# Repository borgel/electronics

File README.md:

Ultimate Hacking Keyboard electronics
=====================================

Contained are the schematics and board layout KiCad files for the [Ultimate Hacking Keyboard](https://ultimatehackingkeyboard.com/).

Please make sure to clone this repo with:

`git clone --recursive git@github.com:borgel/electronics.git`

Now, you should be able to open any of the 4 [KiCad](http://kicad-pcb.org/) projects of the repo:

* [left-main](left-main) contains main PCB of left keyboard half.
* [right-main](right-main) contains the main PCB of the right keyboard half.
* [display](display) contains the PCB that interfaces our custom manufactured LED segment display with the left main PCB.
* [connectors](connectors) are very small PCBs that are soldered vertically to the left and right main circuit boards to interconnect the keyboard halves without needing a bridge cable.

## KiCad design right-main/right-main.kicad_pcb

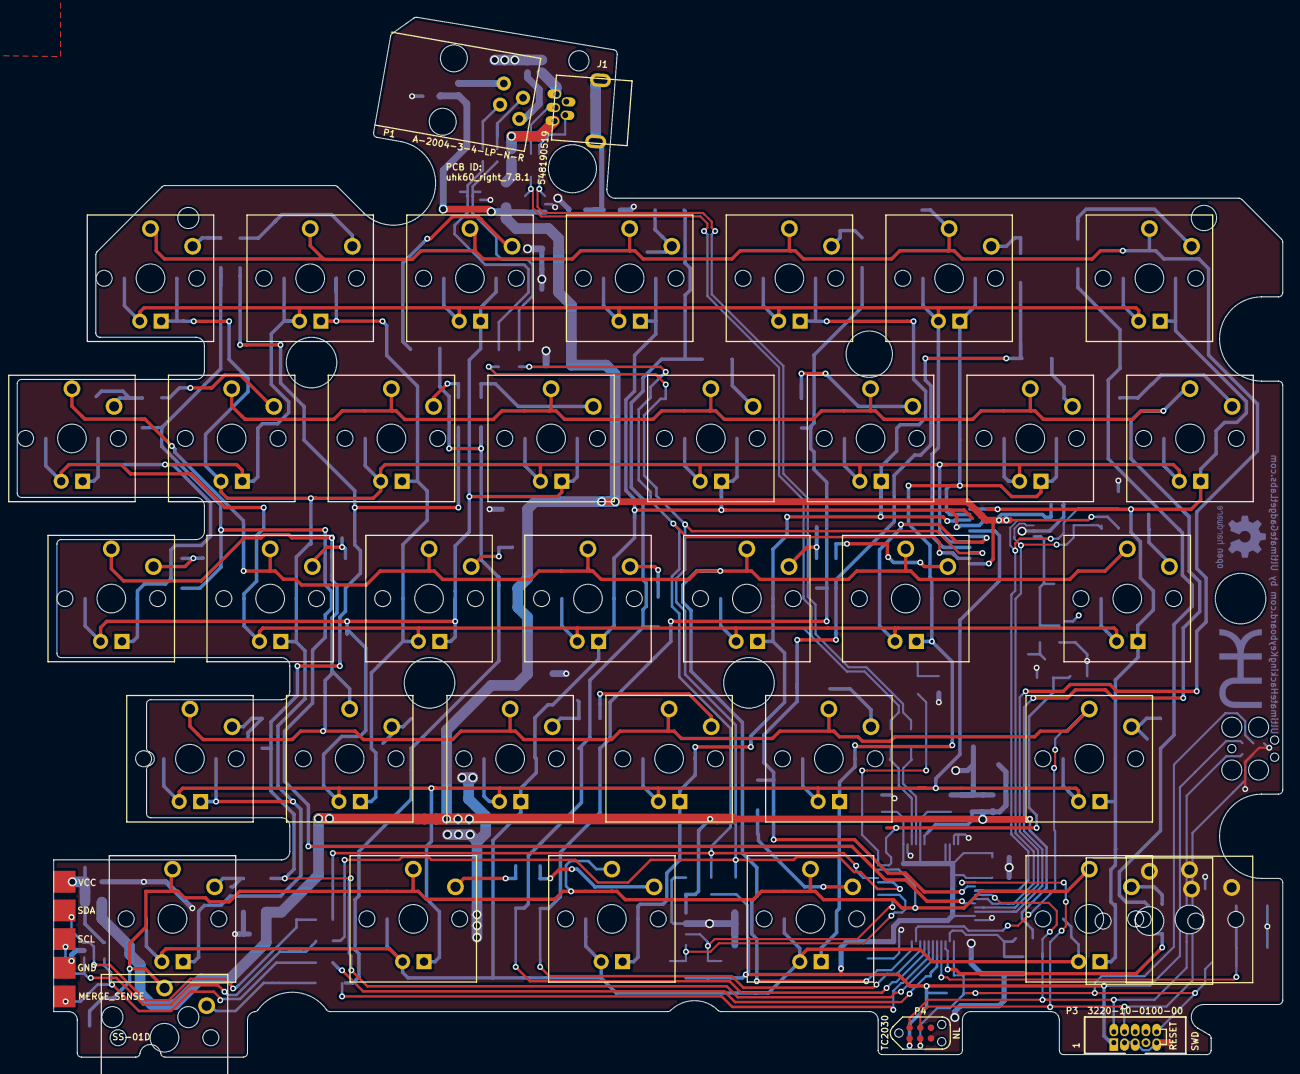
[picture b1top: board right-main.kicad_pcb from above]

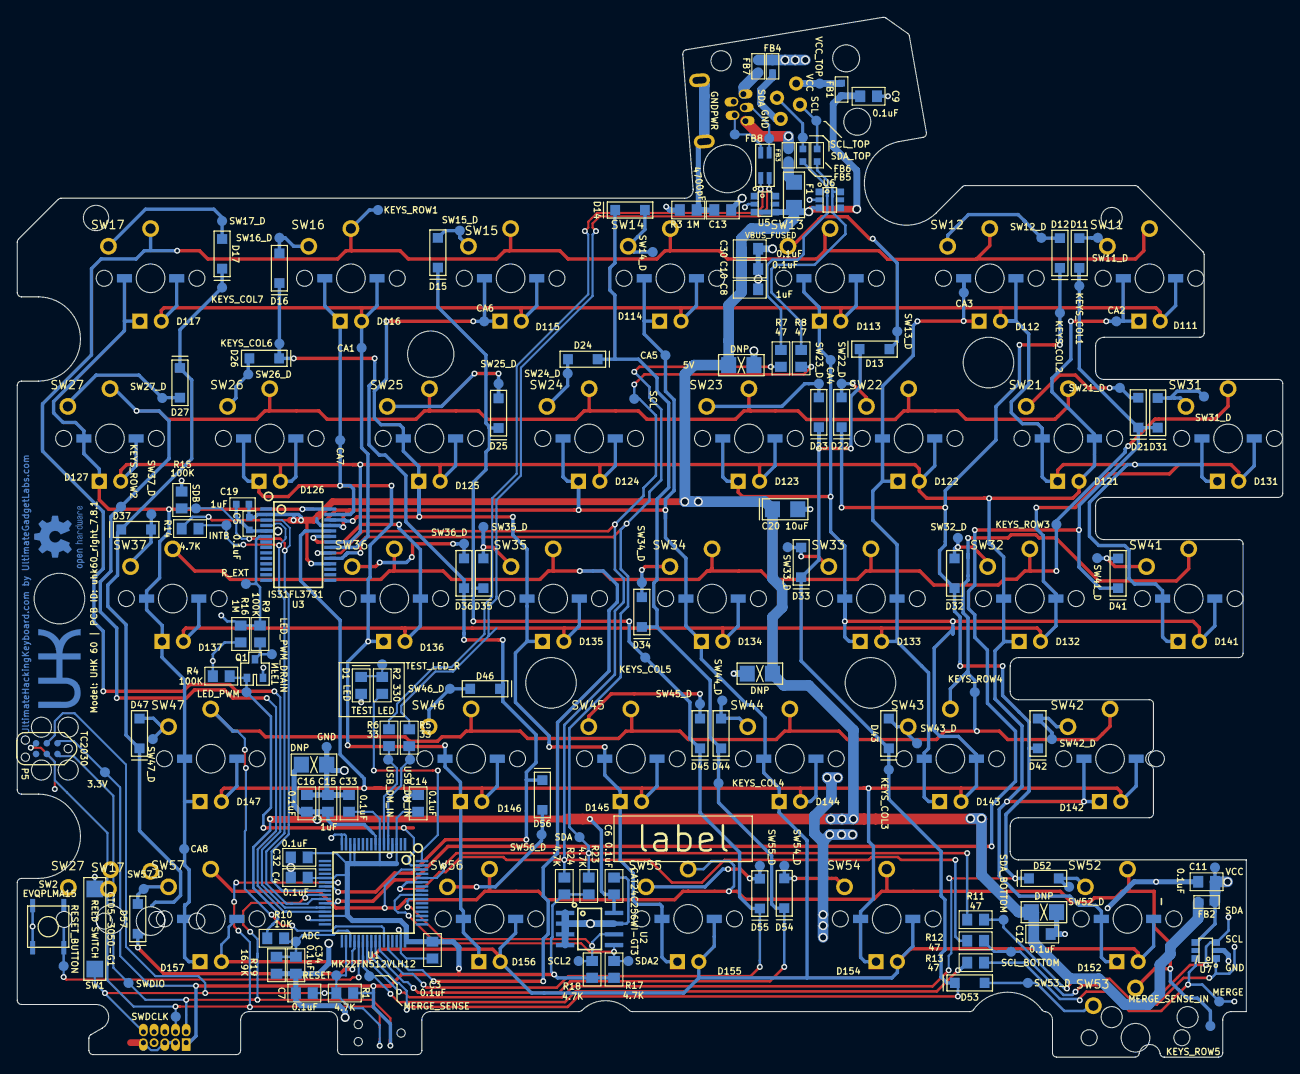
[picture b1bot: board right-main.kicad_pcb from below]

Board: 2 copper layers, 150.1 x 123.4 mm, 273 parts (221 on the bottom side), 94 nets.

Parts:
C3, C4, C6, C7, C9, C10, C11, C12, C14, C16, C30, C32, C33, C34: 0.1uF; SM0805
C5: 0.1uF; SM0603
C8, C15: 1uF; SM0805
C13: 4700pF; SM0805
C19: 1uF; SM0603
C20: 10uF; SM1206_Diode
C22, C23, C24, C25: DNP; SM1206_DNP
D1: LED; SM0805_Diode
D11, D12, D13, D14, D15, D16, D17, D21, D22, D23, D24, D25, D26, D27, D31, D32, D33, D34, D35, D36, D37, D41, D42, D43, D44, D45, D46, D47, D52, D53, D54, D55, D56, D57: DIODE; SOD-123_Diode
D111, D112, D113, D114, D115, D116, D117, D121, D122, D123, D124, D125, D126, D127, D131, D132, D133, D134, D135, D136, D137, D141, D142, D143, D144, D145, D146, D147, D152, D154, D155, D156, D157: LED; Cherry_MX_LED
F1: FUSE; SM1206
FB1, FB2, FB3, FB4, FB5, FB6, FB7: FERRITE_BEAD; SM0603
FB8: FERRITE_BEAD_COMMON_MODE; Wurth_744232090
G1: LOGO; UHK_Logo_5mm_height
G2: LOGO; OSHW_Logo_6mm_height_BCu
J1: 548190519; USB_Mini_B_Connector_0548190519
LABEL1: label
P1: A-2004-3-4-LP-N-R; 4P4C_Jack_A-2004-3-4-LP-N-R
P2: CONN_5; UHK_Connector_Right_PCB
P3: 3220-10-0100-00; 2x5_0.05_pitch_pin_shrouded_header_min
P4: CONN_6; Tag_Connect_2x3_Header_No_Legs
P5: CONN_6; Tag_Connect_2x3_Header_With_Legs
Q1: MOSFET_N; SOT-23-GSD
R1, R14, R17, R18, R23, R24: 4.7K; SM0805
R2: 330; SM0805
R3, R16: 1M; SM0805
R4, R9, R15: 100K; SM0805
R5, R6: 33; SM0805
R7, R8, R11, R12, R13: 47; SM0805
R10: 10K; SM0805
R19: 16.9K; SM0805
SW1: CT05-3050-G1; Reed_Switch_CT05-3050-G1
SW2: EVQPLMA15
SW11: 7; CPG135001D02
SW12: 8; CPG135001D02
SW13: 9; CPG135001D02
SW14: 0; CPG135001D02
SW15: -; CPG135001D02
SW16: =; CPG135001D02
SW17, SW17#2: BACKSPACE; CPG135001D02
SW21: U; CPG135001D02
SW22: I; CPG135001D02
SW23: O; CPG135001D02
SW24: P; CPG135001D02
SW25: [; CPG135001D02
SW26: ]; CPG135001D02
SW27, SW27#2: \; CPG135001D02
SW31: Y; CPG135001D02
SW32: J; CPG135001D02
SW33: K; CPG135001D02
SW34: L; CPG135001D02
SW35: ;; CPG135001D02
SW36: '; CPG135001D02
SW37: ENTER; CPG135001D02
SW41: H; CPG135001D02
SW42: N; CPG135001D02
SW43: M; CPG135001D02
SW44: ,; CPG135001D02
SW45: .; CPG135001D02
SW46: /; CPG135001D02
SW47: R_SHIFT; CPG135001D02
SW52: R_SPACE; CPG135001D02
SW53: R_MOD; CPG135001D02
SW54: R_FN; CPG135001D02
SW55: R_ALT; CPG135001D02
SW56: R_SUPER; CPG135001D02
SW57: R_CTRL; CPG135001D02
TP_3.3V1: 3.3V; Test_Point
TP_5V1: 5V; Test_Point
TP_ADC1: ADC; Test_Point
TP_CA1: CA1; Test_Point
TP_CA2: CA2; Test_Point
TP_CA3: CA3; Test_Point
TP_CA4: CA4; Test_Point
TP_CA5: CA5; Test_Point
TP_CA6: CA6; Test_Point
TP_CA7: CA7; Test_Point
TP_CA8: CA8; Test_Point
TP_GND1: GND; Test_Point
TP_GNDPWR1: GNDPWR; Test_Point
TP_INTB1: INTB; Test_Point
TP_KEYS_COL1: KEYS_COL1; Test_Point
TP_KEYS_COL2: KEYS_COL2; Test_Point
TP_KEYS_COL3: KEYS_COL3; Test_Point
TP_KEYS_COL4: KEYS_COL4; Test_Point
TP_KEYS_COL5: KEYS_COL5; Test_Point
TP_KEYS_COL6: KEYS_COL6; Test_Point
TP_KEYS_COL7: KEYS_COL7; Test_Point
TP_KEYS_ROW1: KEYS_ROW1; Test_Point
TP_KEYS_ROW2: KEYS_ROW2; Test_Point
TP_KEYS_ROW3: KEYS_ROW3; Test_Point
TP_KEYS_ROW4: KEYS_ROW4; Test_Point
TP_KEYS_ROW5: KEYS_ROW5; Test_Point
TP_LED_PWM1: LED_PWM; Test_Point
TP_LED_PWM_DRAIN1: LED_PWM_DRAIN; Test_Point
TP_MERGE_SENSE1: MERGE_SENSE; Test_Point
TP_MERGE_SENSE_IN1: MERGE_SENSE_IN; Test_Point
TP_RESET1: RESET; Test_Point
TP_RESET_BUTTON1: RESET_BUTTON; Test_Point
TP_R_EXT1: R_EXT; Test_Point
TP_SCL1: SCL; Test_Point
TP_SCL2: SCL2; Test_Point
TP_SCL_BOTTOM1: SCL_BOTTOM; Test_Point
TP_SCL_TOP1: SCL_TOP; Test_Point
TP_SDA1: SDA; Test_Point
TP_SDA2: SDA2; Test_Point
TP_SDA_BOTTOM1: SDA_BOTTOM; Test_Point
TP_SDA_TOP1: SDA_TOP; Test_Point
TP_SDB1: SDB; Test_Point
TP_SW11_D1: SW11_D; Test_Point
TP_SW12_D1: SW12_D; Test_Point
TP_SW13_D1: SW13_D; Test_Point
TP_SW14_D1: SW14_D; Test_Point
TP_SW15_D1: SW15_D; Test_Point
TP_SW16_D1: SW16_D; Test_Point
TP_SW17_D1: SW17_D; Test_Point
TP_SW21_D1: SW21_D; Test_Point
TP_SW22_D1: SW22_D; Test_Point
TP_SW23_D1: SW23_D; Test_Point
TP_SW24_D1: SW24_D; Test_Point
TP_SW25_D1: SW25_D; Test_Point
TP_SW26_D1: SW26_D; Test_Point
TP_SW27_D1: SW27_D; Test_Point
TP_SW31_D1: SW31_D; Test_Point
TP_SW32_D1: SW32_D; Test_Point
TP_SW33_D1: SW33_D; Test_Point
TP_SW34_D1: SW34_D; Test_Point
TP_SW35_D1: SW35_D; Test_Point
TP_SW36_D1: SW36_D; Test_Point
TP_SW37_D1: SW37_D; Test_Point
TP_SW41_D1: SW41_D; Test_Point
TP_SW42_D1: SW42_D; Test_Point
TP_SW43_D1: SW43_D; Test_Point
TP_SW44_D1: SW44_D; Test_Point
TP_SW45_D1: SW45_D; Test_Point
TP_SW46_D1: SW46_D; Test_Point
TP_SW47_D1: SW47_D; Test_Point
TP_SW52_D1: SW52_D; Test_Point
TP_SW53_D1: SW53_D; Test_Point
TP_SW54_D1: SW54_D; Test_Point
TP_SW55_D1: SW55_D; Test_Point
TP_SW56_D1: SW56_D; Test_Point
TP_SW57_D1: SW57_D; Test_Point
TP_SWDCLK1: SWDCLK; Test_Point
TP_SWDIO1: SWDIO; Test_Point
TP_TEST_LED_R1: TEST_LED_R; Test_Point
TP_USB_DM1: USB_DM_IN; Test_Point
TP_USB_DM_IN1: USB_DM_IN; Test_Point
TP_USB_DP1: USB_DM_IN; Test_Point
TP_USB_DP_IN1: USB_DP_IN; Test_Point
TP_VBUS_FUSED1: VBUS_FUSED; Test_Point
TP_VCC_BOTTOM1: VCC_BOTTOM; Test_Point
TP_VCC_TOP1: VCC_TOP; Test_Point
U1: MK22FN512VLH12; LQFP64
U2: CAT24C256WI-GT3; EEPROM-SOIC8
U3: IS31FL3731; SSOP-28
U5, U6, U7: ESD; SC-74-TVS
hole: 6mm; hole_5.5mm
hole#2: 2.6mm; hole_2.4mm
hole#3, hole#4, hole#5, hole#6: 6mm; hole_6mm
hole#7: 5.7mm; hole_5.7mm
hole#8, hole#10, hole#11: 2.5mm; hole_2.5mm
hole#9: 3mm; hole_3mm

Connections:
+3V3: C3.2, C4.1, C14.2, C32.2, C33.2, P3.1, P4.1, P5.1, R1.1, R17.1, R18.1, R23.1, R24.1, TP_3.3V1.1, U1.3, U1.7, U1.13, U1.14, U1.21, U1.30, U1.48
+5V: C5.2, C6.2, C8.2, C9.2, C10.2, C12.2, C15.2, C16.2, C19.2, C20.1, C22.2, C23.2, C24.2, C25.2, C30.2, F1.1, FB1.2, FB2.2, R10.1, R14.1, TP_5V1.1, TP_VBUS_FUSED1.1, U1.8, U2.8, U3.2, U3.18, U5.3, U5.4, U6.3
/ADC: C34.2, R10.2, R19.1, TP_ADC1.1, U1.35
/CA1: D111.2, D112.2, D113.2, D114.2, D115.2, D116.2, D117.2, D121.1, D131.1, D141.1, TP_CA1.1, U3.21
/CA2: D111.1, D121.2, D122.2, D123.2, D124.2, D125.2, D126.2, D127.2, D132.1, D142.1, D152.1, TP_CA2.1, U3.22
/CA3: D112.1, D122.1, D131.2, D132.2, D133.2, D134.2, D135.2, D136.2, D137.2, D143.1, TP_CA3.1, U3.23
/CA4: D113.1, D123.1, D133.1, D141.2, D142.2, D143.2, D144.2, D145.2, D146.2, D147.2, D154.1, TP_CA4.1, U3.24
/CA5: D114.1, D124.1, D134.1, D144.1, D152.2, D154.2, D155.2, D156.2, D157.2, TP_CA5.1, U3.25
/CA6: D115.1, D125.1, D135.1, D145.1, D155.1, TP_CA6.1, U3.26
/CA7: D116.1, D126.1, D136.1, D146.1, D156.1, TP_CA7.1, U3.27
/CA8: D117.1, D127.1, D137.1, D147.1, D157.1, TP_CA8.1, U3.28
/GND_IN: FB7.1, J1.4
/GND_TOP: FB4.1, P1.1
/INTB: R14.2, TP_INTB1.1, U1.26, U3.4
/KEYS_COL1: D11.2, D21.2, D31.2, D41.2, TP_KEYS_COL1.1, U1.27
/KEYS_COL2: D12.2, D22.2, D32.2, D42.2, D52.2, TP_KEYS_COL2.1, U1.39
/KEYS_COL3: D13.2, D23.2, D33.2, D43.2, D53.2, TP_KEYS_COL3.1, U1.40
/KEYS_COL4: D14.2, D24.2, D34.2, D44.2, D54.2, TP_KEYS_COL4.1, U1.41
/KEYS_COL5: D15.2, D25.2, D35.2, D45.2, D55.2, TP_KEYS_COL5.1, U1.42
/KEYS_COL6: D16.2, D26.2, D36.2, D46.2, D56.2, TP_KEYS_COL6.1, U1.23
/KEYS_COL7: D17.2, D27.2, D37.2, D47.2, D57.2, TP_KEYS_COL7.1, U1.36
/KEYS_ROW1: SW11.1, SW12.1, SW13.1, SW14.1, SW15.1, SW16.1, SW17.1, SW17#2.1, TP_KEYS_ROW1.1, U1.28
/KEYS_ROW2: SW21.1, SW22.1, SW23.1, SW24.1, SW25.1, SW26.1, SW27.1, SW27#2.1, TP_KEYS_ROW2.1, U1.29
/KEYS_ROW3: SW31.1, SW32.1, SW33.1, SW34.1, SW35.1, SW36.1, SW37.1, TP_KEYS_ROW3.1, U1.44
/KEYS_ROW4: SW41.1, SW42.1, SW43.1, SW44.1, SW45.1, SW46.1, SW47.1, TP_KEYS_ROW4.1, U1.43
/KEYS_ROW5: SW52.1, SW53.1, SW54.1, SW55.1, SW56.1, SW57.1, TP_KEYS_ROW5.1, U1.62
/LED_PWM: Q1.G, R4.2, TP_LED_PWM1.1, U1.63
/LED_PWM_DRAIN: Q1.D, R9.2, TP_LED_PWM_DRAIN1.1
/MERGE_SENSE: R13.1, TP_MERGE_SENSE1.1, U1.38
/MERGE_SENSE_IN: P2.5, R13.2, TP_MERGE_SENSE_IN1.1, U7.5
/RESET: C7.2, P3.10, P4.3, P5.3, R1.2, SW1.1, TP_RESET1.1, U1.34
/RESET_BUTTON: SW2.2, TP_RESET_BUTTON1.1, U1.37
/R_EXT: R9.1, R16.1, TP_R_EXT1.1, U3.6
/SCL: R8.1, R12.1, R24.2, TP_SCL1.1, U1.59, U3.20
/SCL2: R18.2, TP_SCL2.1, U1.55, U2.6
/SCL_BOTTOM: P2.3, R12.2, TP_SCL_BOTTOM1.1, U7.1
/SCL_MID: FB6.2, R8.2, U6.5
/SCL_TOP: FB6.1, P1.2, TP_SCL_TOP1.1
/SDA: R7.1, R11.1, R23.2, TP_SDA1.1, U1.60, U3.19
/SDA2: R17.2, TP_SDA2.1, U1.56, U2.5
/SDA_BOTTOM: P2.2, R11.2, TP_SDA_BOTTOM1.1, U7.3
/SDA_MID: FB5.2, R7.2, U6.1
/SDA_TOP: FB5.1, P1.3, TP_SDA_TOP1.1
/SDB: R15.1, TP_SDB1.1, U1.24, U3.3
/SW11_D: D11.1, SW11.2, TP_SW11_D1.1
/SW12_D: D12.1, SW12.2, TP_SW12_D1.1
/SW13_D: D13.1, SW13.2, TP_SW13_D1.1
/SW14_D: D14.1, SW14.2, TP_SW14_D1.1
/SW15_D: D15.1, SW15.2, TP_SW15_D1.1
/SW16_D: D16.1, SW16.2, TP_SW16_D1.1
/SW17_D: D17.1, SW17.2, SW17#2.2, TP_SW17_D1.1
/SW21_D: D21.1, SW21.2, TP_SW21_D1.1
/SW22_D: D22.1, SW22.2, TP_SW22_D1.1
/SW23_D: D23.1, SW23.2, TP_SW23_D1.1
/SW24_D: D24.1, SW24.2, TP_SW24_D1.1
/SW25_D: D25.1, SW25.2, TP_SW25_D1.1
/SW26_D: D26.1, SW26.2, TP_SW26_D1.1
/SW27_D: D27.1, SW27.2, SW27#2.2, TP_SW27_D1.1
/SW31_D: D31.1, SW31.2, TP_SW31_D1.1
/SW32_D: D32.1, SW32.2, TP_SW32_D1.1
/SW33_D: D33.1, SW33.2, TP_SW33_D1.1
/SW34_D: D34.1, SW34.2, TP_SW34_D1.1
/SW35_D: D35.1, SW35.2, TP_SW35_D1.1
/SW36_D: D36.1, SW36.2, TP_SW36_D1.1
/SW37_D: D37.1, SW37.2, TP_SW37_D1.1
/SW41_D: D41.1, SW41.2, TP_SW41_D1.1
/SW42_D: D42.1, SW42.2, TP_SW42_D1.1
/SW43_D: D43.1, SW43.2, TP_SW43_D1.1
/SW44_D: D44.1, SW44.2, TP_SW44_D1.1
/SW45_D: D45.1, SW45.2, TP_SW45_D1.1
/SW46_D: D46.1, SW46.2, TP_SW46_D1.1
/SW47_D: D47.1, SW47.2, TP_SW47_D1.1
/SW52_D: D52.1, SW52.2, TP_SW52_D1.1
/SW53_D: D53.1, SW53.2, TP_SW53_D1.1
/SW54_D: D54.1, SW54.2, TP_SW54_D1.1
/SW55_D: D55.1, SW55.2, TP_SW55_D1.1
/SW56_D: D56.1, SW56.2, TP_SW56_D1.1
/SW57_D: D57.1, SW57.2, TP_SW57_D1.1
/SWDCLK: P3.4, P4.4, P5.4, TP_SWDCLK1.1, U1.22
/SWDIO: P3.2, P4.2, P5.2, TP_SWDIO1.1, U1.25
/TEST_LED_R: D1.2, R2.2, TP_TEST_LED_R1.1
/USB_D+: R5.1, TP_USB_DP1.1, U1.5
/USB_D-: R6.1, TP_USB_DM1.1, U1.6
/USB_D_IN+: FB8.4, J1.3, TP_USB_DP_IN1.1
/USB_D_IN-: FB8.1, J1.2, TP_USB_DM_IN1.1
/USB_D_MID+: FB8.3, R5.2, U5.5
/USB_D_MID-: FB8.2, R6.2, U5.1
/VBUS: FB3.1, J1.1
/VBUS_MID: F1.2, FB3.2
/VCC_BOTTOM: C11.2, FB2.1, P2.1, TP_VCC_BOTTOM1.1, U7.4
/VCC_TOP: FB1.1, P1.4, TP_VCC_TOP1.1
GND: C3.1, C4.2, C5.1, C6.1, C7.1, C8.1, C9.1, C10.1, C11.1, C12.1, C13.2, C14.1, C15.1, C16.1, C19.1, C20.2, C22.1, C23.1, C24.1, C25.1, C30.1, C32.1, C33.1, C34.1, D1.1, FB4.2, FB7.2, P2.4, P3.3, P3.5, P3.9, P4.5, P5.5, Q1.S, R3.1, R4.1, R15.2, R16.2, R19.2, SW1.2, SW2.1, TP_GND1.1, U1.4, U1.15, U1.16, U1.31, U1.47, U2.1, U2.2, U2.3, U2.4, U2.7, U3.5, U5.2, U6.2, U7.2
GNDPWR: C13.1, J1.5, R3.2, TP_GNDPWR1.1
unnamed: R2.1, U1.64

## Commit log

2019-05-27 Add @borgel's KiCAD libs submodule
2019-05-28 Right switches changed to Choc, relayout mostly complete
2019-05-28 Update README to refer to my GH account
2019-05-30 Finish integrating Choc into right side
2019-06-02 Playing with movement of switches
